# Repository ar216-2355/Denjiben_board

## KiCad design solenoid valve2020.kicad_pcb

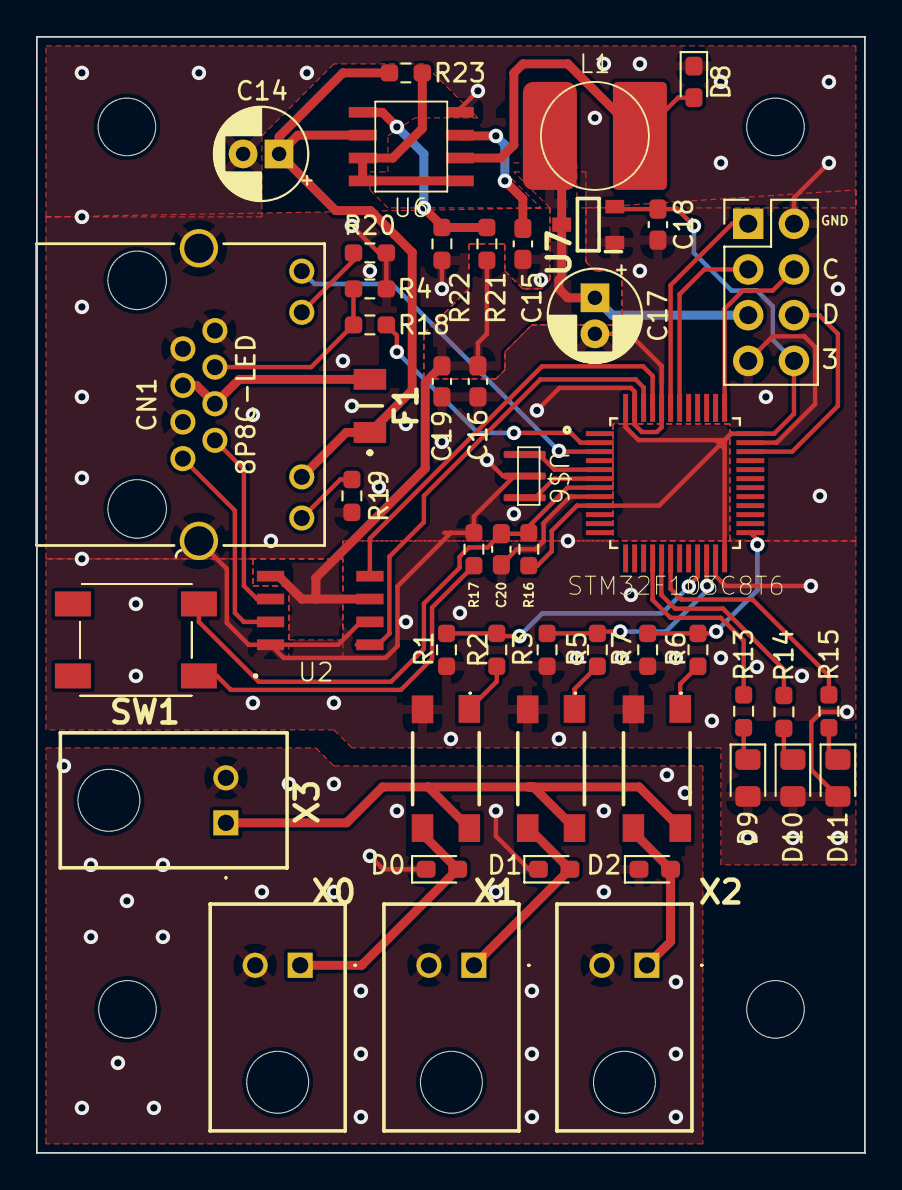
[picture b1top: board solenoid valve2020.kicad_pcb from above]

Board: 2 copper layers, 46.0 x 62.0 mm, 49 parts (0 on the bottom side), 43 nets.

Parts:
C14, C17: 22u; CP_Radial_D5.0mm_P2.00mm
C15: 220p; C_0603_1608Metric_Pad1.08x0.95mm_HandSolder
C16, C18, C19, C20: 100n; C_0603_1608Metric_Pad1.08x0.95mm_HandSolder
CN1: 8P8C-LED; RJHSE-5381 LAN_port
D0, D1, D2, D8: DIODE-SOD123; D_0603_1608Metric_Pad1.05x0.95mm_HandSolder
D9, D10, D11: LEDCHIPLED_0805; LED_0805_2012Metric_Pad1.15x1.40mm_HandSolder
F1: R-EU_R1206; NANOASMDC035F2
JP1: PINHD-2X4; PinHeader_2x04_P2.54mm_Vertical
L1: L5852
R1, R3, R7, R16: 10k; R_0603_1608Metric_Pad0.98x0.95mm_HandSolder
R2, R5, R6, R17: 100R; R_0603_1608Metric_Pad0.98x0.95mm_HandSolder
R4: 100k; R_0603_1608Metric_Pad0.98x0.95mm_HandSolder
R13, R14, R15, R18, R20: 1k; R_0603_1608Metric_Pad0.98x0.95mm_HandSolder
R19: 4k7; R_0603_1608Metric_Pad0.98x0.95mm_HandSolder
R21: 3.6k; R_0603_1608Metric_Pad0.98x0.95mm_HandSolder
R22: 1.2k; R_0603_1608Metric_Pad0.98x0.95mm_HandSolder
R23: 0.68; R_0603_1608Metric_Pad0.98x0.95mm_HandSolder
STM32F103C8T6: STM32F103C8; stm32f103c8t6
SW1: SWITCH_TACTILETOP; 430451025836
TLP172AM1, TLP172AM2, TLP172AM3: 11-4M1S
U2: NCV7351D1E
U6: MC34063AD
U7: XC6206
U$6: CSTCE8M00G55
X0, X1, X2, X3: S2B-XASK-1; S02BXASS1LFSN

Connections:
3v3: C18.1, JP1.8, R16.1, STM32F103C8T6.9 (VDDA), STM32F103C8T6.24 (VDD$1), STM32F103C8T6.36 (VDD$2), STM32F103C8T6.48 (VDD$3), U7.2 (VOUT)
5V: C16.1, C17.1, C19.2, JP1.5, L1.2, R21.2, U2.3 (VS), U2.5 (EN), U7.3 (VIN)
+24V: C14.1, CN1.GA (A-G), F1.1, R23.1, U6.6 (VCC)
/can/CANH: CN1.1, U2.7 (CANH)
/can/CANL: CN1.2, U2.6 (CANL)
/mcu/LED0: R13.1, STM32F103C8T6.16 (PA6)
/mcu/LED1: R14.1, STM32F103C8T6.17 (PA7)
/mcu/LED2: R15.1, STM32F103C8T6.18 (PB0)
/mcu/SWCLK: JP1.4, STM32F103C8T6.37 (PA14-JTCK-SWCLK)
/mcu/SWDIO: JP1.6, STM32F103C8T6.34 (PA13-JTMS-SWDIO)
/mcu/UART_RX: JP1.1, STM32F103C8T6.43 (PB7)
/mcu/UART_TX: JP1.3, STM32F103C8T6.42 (PB6)
/mcu/~RESET: C20.2, R16.2, STM32F103C8T6.7 (NRST), SW1.2
CANRX: STM32F103C8T6.45 (PB8), U2.4 (RXD)
CANTX: STM32F103C8T6.46 (PB9), U2.1 (TXD)
GND: D0.A, D1.A, D2.A, X0.2, X1.2, X2.2, X3.2
GNDIO: C14.2, C15.2, C16.2, C17.2, C18.2, C19.1, C20.1, CN1.3, CN1.7, CN1.8, CN1.M1 (SHIELD), CN1.M2 (SHIELD), D8.A, D9.C, D10.C, D11.C, JP1.2, JP1.7, R1.2, R3.2, R4.2, R7.2, R17.2, R19.1, R20.1, R22.1, STM32F103C8T6.8 (VSSA), STM32F103C8T6.23 (VSS$1), STM32F103C8T6.35 (VSS$2), STM32F103C8T6.44 (BOOT0), STM32F103C8T6.47 (VSS$3), TLP172AM1.3, TLP172AM2.3, TLP172AM3.3, U2.2 (GND), U2.8 (S), U6.4 (SWC), U7.1 (VSS), U$6.2
LED_CAN: CN1.YA (A-Y), STM32F103C8T6.3 (PC14-OSC32_IN)
unnamed: CN1.GC (C-G), R19.2
unnamed: CN1.YC (C-Y), R20.2
unnamed: CN1.4, CN1.5, F1.2
unnamed: CN1.6, R4.1, R18.2
unnamed: D0.C, TLP172AM3.4, X0.1
unnamed: D1.C, TLP172AM1.4, X1.1
unnamed: D2.C, TLP172AM2.4, X2.1
unnamed: D9.A, R13.2
unnamed: D10.A, R14.2
unnamed: D11.A, R15.2
unnamed: R2.2, TLP172AM3.1
unnamed: R5.2, TLP172AM1.1
unnamed: R6.2, TLP172AM2.1
unnamed: R17.1, SW1.1
unnamed: STM32F103C8T6.5 (OSC_IN), U$6.1
unnamed: STM32F103C8T6.6 (OSC_OUT), U$6.3
unnamed: R23.2, U6.1 (GND), U6.7 (IS), U6.8 (DC)
unnamed: R21.1, R22.2, U6.5 (FB)
unnamed: D8.C, L1.1, U6.2 (TC)
unnamed: C15.1, U6.3 (SWE)
SOLV0: R1.1, R2.1, STM32F103C8T6.21 (PB10)
SOLV1: R3.1, R5.1, STM32F103C8T6.22 (PB11)
SOLV2: R6.1, R7.1, STM32F103C8T6.25 (PB12)
VCC: TLP172AM1.6, TLP172AM2.6, TLP172AM3.6, X3.1
~EMS: R18.1, STM32F103C8T6.2 (PC13-TAMPER-RTC)

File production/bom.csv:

Designator,Footprint,Quantity,Value,LCSC Part #
"C14, C17",CP_Radial_D5.0mm_P2.00mm,2,22u,
C15,0603,1,220p,
"C16, C18, C19, C20",0603,4,100n,
CN1,RJHSE-5381 LAN_port,1,8P8C-LED,
"D0, D1, D2, D8",0603,4,DIODE-SOD123,
"D10, D11, D9",0805,3,LEDCHIPLED_0805,
F1,NANOASMDC035F2,1,R-EU_R1206,
JP1,PinHeader_2x04_P2.54mm_Vertical,1,PINHD-2X4,
L1,L5852,1,L5852,
"R1, R16, R3, R7",0603,4,10k,
"R13, R14, R15, R18, R20",0603,5,1k,
"R17, R2, R5, R6",0603,4,100R,
R19,0603,1,4k7,
R21,0603,1,3.6k,
R22,0603,1,1.2k,
R23,0603,1,0.68,
R4,0603,1,100k,
STM32F103C8T6,stm32f103c8t6,1,STM32F103C8,
SW1,430451025836,1,SWITCH_TACTILETOP,
"TLP172AM1, TLP172AM2, TLP172AM3",11-4M1S,3,~,
U$6,CSTCE8M00G55,1,CSTCE8M00G55,
U2,NCV7351D1E,1,NCV7351D1E,
U6,MC34063AD,1,MC34063AD,
U7,XC6206,1,XC6206,
"X0, X1, X2, X3",S02BXASS1LFSN,4,S2B-XASK-1,

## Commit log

2026-01-08 rewqqq

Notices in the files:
parts and their libraries:
Copyright 2016 Accelerated Designs. All rights reserved.
